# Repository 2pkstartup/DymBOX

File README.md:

# DymBOX

Regulátor teploty pro udírnu postavený na mikrokontroléru **ATmega8**.

Měří teplotu pomocí DS18B20, zobrazuje ji na 3-místném 7-segmentovém displeji a řídí ventilátor (PWM) a topnou spirálu (ON/OFF s hysterezí). Žádaná teplota a otáčky ventilátoru se nastavují rotačním enkodérem.

## Vlastnosti

- **Měření teploty** – DS18B20 (1-Wire), rozlišení 0.1 °C
- **3-místný 7-segment display** – multiplexovaný v Timer0 ISR (~163 Hz/číslice)
- **Rotační enkodér KY-040** – nastavení žádané teploty a otáček ventilátoru
- **PWM ventilátor** – 11 kroků (0–100 % po 10 %), Timer1 Fast PWM 8-bit na ~977 Hz
- **Topná spirála** – ON/OFF regulace s hysterezí 5 °C
- **Nastavitelný setpoint** – výchozí 32.0 °C, editace po 0.1 °C

## Struktura repozitáře

```
DymBOX/
├── fw/                 # Firmware (C, ATmega8)
│   ├── main.c
│   ├── CMakeLists.txt
│   ├── Makefile
│   ├── cmake/          # AVR-GCC toolchain soubor
│   └── README.md
├── hw/                 # Hardware (KiCad 8)
│   ├── DymBOX_AVR.kicad_sch    # Schéma
│   ├── DymBOX_AVR.kicad_pcb    # PCB layout
│   ├── gerber/                  # Gerber soubory pro výrobu
│   ├── dymbox_gerber.zip        # Zabalené gerbery
│   ├── 2pkstartup.pretty/      # Vlastní footprinty
│   └── DymBOX_AVR-backups/
└── README.md
```

## Hardware

Schéma a PCB jsou navrženy v **KiCadu**. Gerber soubory připravené k výrobě najdete v `hw/gerber/` nebo jako `hw/dymbox_gerber.zip`.

### Hlavní komponenty

| Součástka | Popis |
|-----------|-------|
| ATmega8 | Hlavní MCU (16 MHz) |
| DS18B20 | Digitální teploměr (1-Wire) |
| 3× 7-segment (common anode) | Displej – multiplexovaný |
| KY-040 | Rotační enkodér s tlačítkem |
| Ventilátor | PWM řízený (~977 Hz) |
| Topná spirála | ON/OFF přes PB2 |

### Zapojení pinů

```
PORTB: PB0 = seg A       PB1 = PWM fan    PB2 = heater
PORTC: PC0 = seg E       PC1 = seg D      PC2 = seg DP
       PC3 = seg C       PC4 = seg G      PC5 = DS18B20
PORTD: PD0 = ENC SW      PD1 = DIG3       PD2 = DIG2
       PD3 = ENC CLK     PD4 = ENC DT     PD5 = DIG1
       PD6 = seg B       PD7 = seg F
```

## Firmware

Firmware je napsaný v **C** pro AVR a překládá se pomocí `avr-gcc` + CMake.

### Požadavky

```bash
sudo apt install gcc-avr avr-libc binutils-avr avrdude cmake
```

### Kompilace a nahrání

```bash
cd fw
cmake -B build -DCMAKE_TOOLCHAIN_FILE=cmake/avr-gcc.cmake
cmake --build build              # Kompilace
cmake --build build --target flash   # Nahrání do MCU (USBasp)
cmake --build build --target fuses   # Nastavení fuses
```

### Velikost firmware

```
Program:  ~2186 bytes (26.7 % Flash)
Data:       ~61 bytes  (6.0 % SRAM)
```

## Ovládání

Zařízení má 3 režimy zobrazení:

| Režim | Displej | Ovládání |
|-------|---------|----------|
| **Teplota** (výchozí) | `XX.X` – aktuální teplota | Otočení → ventilátor · Stisk → editace setpointu |
| **Ventilátor** | `FXX` – rychlost v % | Otočení → změna po 10 % · Po 2 s → zpět na teplotu |
| **Editace setpointu** | `XX.X` + DP1 svítí | Otočení → změna po 0.1 °C · Stisk → uložit a zpět |

Topná spirála se indikuje rozsvícením DP3 (poslední tečka).

## Regulace teploty

ON/OFF regulace s hysterezí:

| Podmínka | Akce |
|----------|------|
| teplota ≤ setpoint − 5 °C | Spirála **ON** |
| teplota ≥ setpoint | Spirála **OFF** |
| v pásmu hystereze | Beze změny |

## Licence

Tento projekt je volně k použití.

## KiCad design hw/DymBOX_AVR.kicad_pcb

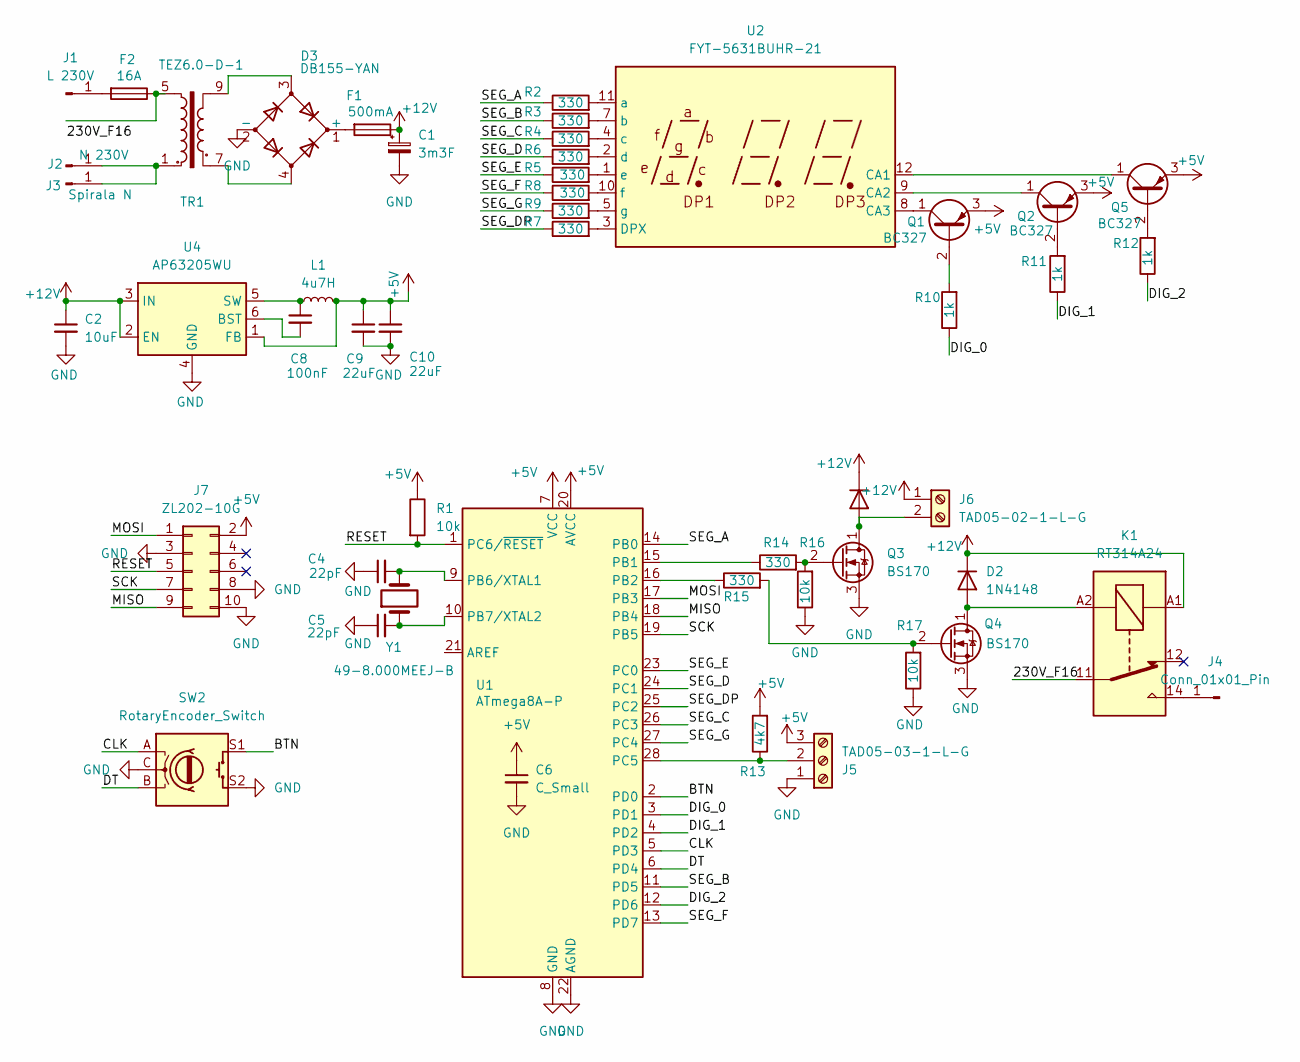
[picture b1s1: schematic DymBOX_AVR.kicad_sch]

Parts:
C1: 3m3F; CP_Radial_D16.0mm_P7.50mm
C2: 10uF; C_1206_3216Metric_Pad1.33x1.80mm_HandSolder
C4, C5: 22pF; C_0805_2012Metric_Pad1.18x1.45mm_HandSolder
C6: C_Small; C_0805_2012Metric_Pad1.18x1.45mm_HandSolder
C8: 100nF; C_0805_2012Metric_Pad1.18x1.45mm_HandSolder
C9, C10: 22uF; C_0805_2012Metric_Pad1.18x1.45mm_HandSolder
D1, D2: 1N4148; D_DO-35_SOD27_P7.62mm_Horizontal
D3: DB155-YAN; Diode_Bridge_DIP-4_W5.08mm_P2.54mm
F1: 500mA; Fuseholder_Clip-5x20mm_Littelfuse_111_Inline_P20.00x5.00mm_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
F2: 16A; Fuseholder_Clip-5x20mm_Littelfuse_111_Inline_P20.00x5.00mm_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
J1: L 230V; faston_6.3
J2: N 230V; faston_6.3
J3: Spirala N; faston_6.3
J4: Conn_01x01_Pin; faston_6.3
J5: TAD05-03-1-L-G; TerminalBlock_Phoenix_PT-1,5-3-3.5-H_1x03_P3.50mm_Horizontal
J6: TAD05-02-1-L-G; TerminalBlock_Phoenix_PT-1,5-2-3.5-H_1x02_P3.50mm_Horizontal
J7: ZL202-10G; PinHeader_2x05_P2.54mm_Vertical
K1: RT314A24; Relay_SPDT_Schrack-RT1-16A-FormC_RM5mm
L1: 4u7H; L_1210_3225Metric_Pad1.42x2.65mm_HandSolder
Q1, Q2, Q5: BC327; TO-92_HandSolder
Q3, Q4: BS170; TO-92_HandSolder
R1, R16, R17: 10k; R_Axial_DIN0204_L3.6mm_D1.6mm_P5.08mm_Horizontal
R2, R3, R4, R5, R6, R7, R8, R9, R14, R15: 330; R_Axial_DIN0204_L3.6mm_D1.6mm_P5.08mm_Horizontal
R10, R11, R12: 1k; R_Axial_DIN0204_L3.6mm_D1.6mm_P5.08mm_Horizontal
R13: 4k7; R_Axial_DIN0204_L3.6mm_D1.6mm_P5.08mm_Horizontal
SW2: RotaryEncoder_Switch; RotaryEncoder_Alps_EC12E-Switch_Vertical_H20mm_CircularMoun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
TR1: TEZ6.0-D-1; Transformer_Breve_TEZ-38x45
U1: ATmega8A-P; DIP-28_W7.62mm
U2: FYT-5631BUHR-21
U4: AP63205WU; TSOT-23-6
Y1: 49-8.000MEEJ-B; Crystal_HC49-U_Vertical

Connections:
+5V: C6.1, C9.1, C10.1, J5.3, J7.2, L1.2, Q1.3 (E), Q2.3 (E), Q5.3 (E), R1.1, R13.2, U1.7 (VCC), U1.20 (AVCC), U4.1 (FB)
+12V: C1.1, C2.1, D1.1 (K), D2.1 (K), F1.1, J6.1, K1.A1, U4.2 (EN), U4.3 (IN)
/BTN: SW2.S1, U1.2 (PD0)
/CLK: SW2.A, U1.5 (PD3)
/DIG_0: R10.1, U1.3 (PD1)
/DIG_1: R11.1, U1.4 (PD2)
/DIG_2: R12.1, U1.12 (PD6)
/DT: SW2.B, U1.6 (PD4)
/MISO: J7.9, U1.18 (PB4)
/MOSI: J7.1, U1.17 (PB3)
/RESET: J7.5, R1.2, U1.1 (PC6/~RESET)
/SCK: J7.7, U1.19 (PB5)
/SEG_A: R2.1, U1.14 (PB0)
/SEG_B: R3.1, U1.11 (PD5)
/SEG_C: R4.1, U1.26 (PC3)
/SEG_D: R6.1, U1.24 (PC1)
/SEG_DP: R7.1, U1.25 (PC2)
/SEG_E: R5.1, U1.23 (PC0)
/SEG_F: R8.1, U1.13 (PD7)
/SEG_G: R9.1, U1.27 (PC4)
GND: C1.2, C2.2, C4.1, C5.1, C6.2, C9.2, C10.2, D3.2 (-), J5.1, J7.3, J7.8, J7.10, Q3.3 (S), Q4.3 (S), R16.1, R17.1, SW2.C, SW2.S2, U1.8 (GND), U1.22 (AGND), U4.4 (GND)
unnamed: D1.2 (A), J6.2, Q3.1 (D)
unnamed: D2.2 (A), K1.A2, Q4.1 (D)
unnamed: D3.1 (+), F1.2
unnamed: D3.3, TR1.9
unnamed: D3.4, TR1.7
unnamed: F2.2, J1.1 (Pin_1_1)
unnamed: J2.1 (Pin_1_1), J3.1 (Pin_1_1), TR1.1
unnamed: J4.1 (Pin_1_1), K1.14
unnamed: J5.2, R13.1, U1.28 (PC5)
unnamed: Q1.2 (B), R10.2
unnamed: Q1.1 (C), U2.8 (CA3)
unnamed: Q2.2 (B), R11.2
unnamed: Q2.1 (C), U2.9 (CA2)
unnamed: Q3.2 (G), R14.2, R16.2
unnamed: Q4.2 (G), R15.2, R17.2
unnamed: Q5.2 (B), R12.2
unnamed: Q5.1 (C), U2.12 (CA1)
unnamed: R14.1, U1.15 (PB1)
unnamed: R15.1, U1.16 (PB2)
unnamed: C4.2, U1.9 (PB6/XTAL1), Y1.2
unnamed: C5.2, U1.10 (PB7/XTAL2), Y1.1
unnamed: R7.2, U2.3 (DPX)
unnamed: R2.2, U2.11 (a)
unnamed: R3.2, U2.7 (b)
unnamed: R4.2, U2.4 (c)
unnamed: R6.2, U2.2 (d)
unnamed: R5.2, U2.1 (e)
unnamed: R8.2, U2.10 (f)
unnamed: R9.2, U2.5 (g)
unnamed: C8.2, U4.6 (BST)
unnamed: C8.1, L1.1, U4.5 (SW)

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
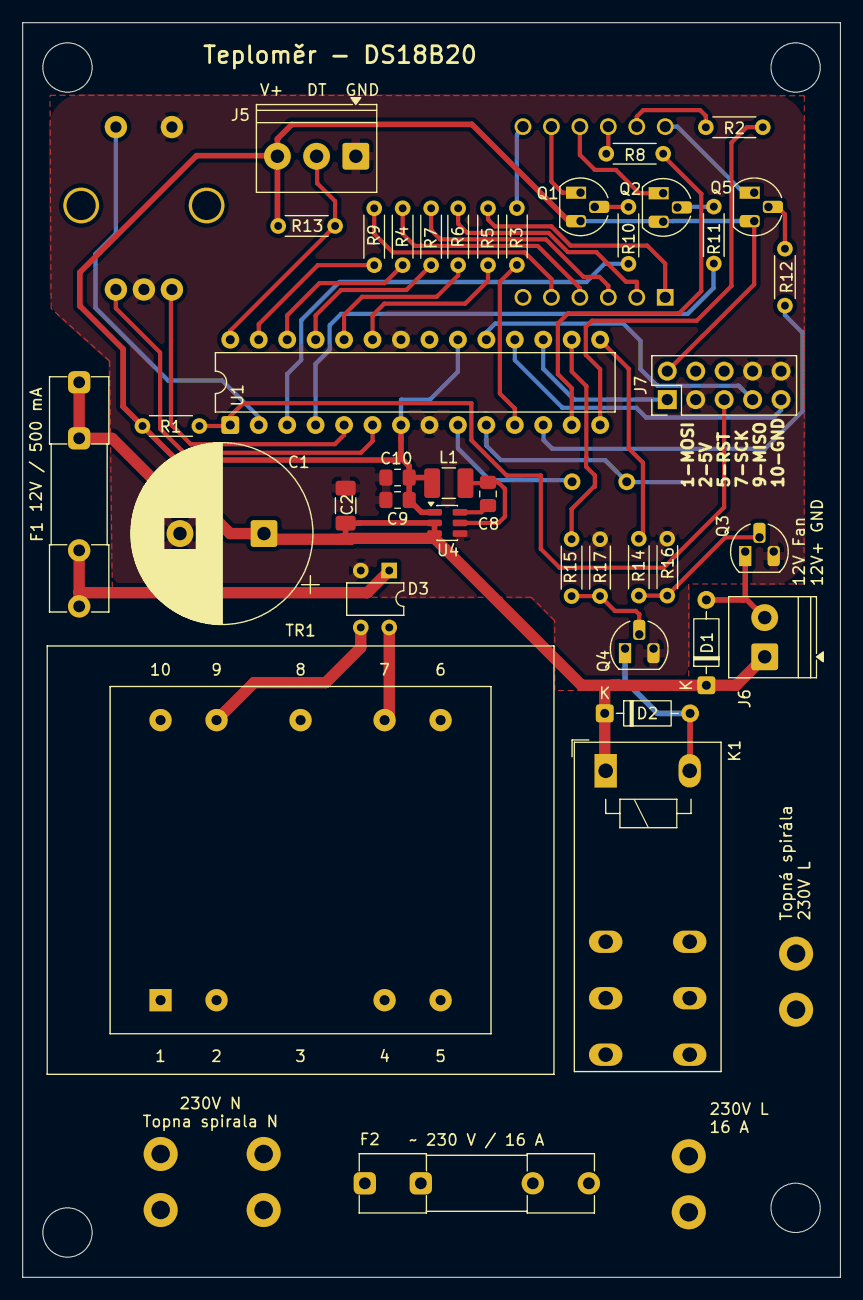
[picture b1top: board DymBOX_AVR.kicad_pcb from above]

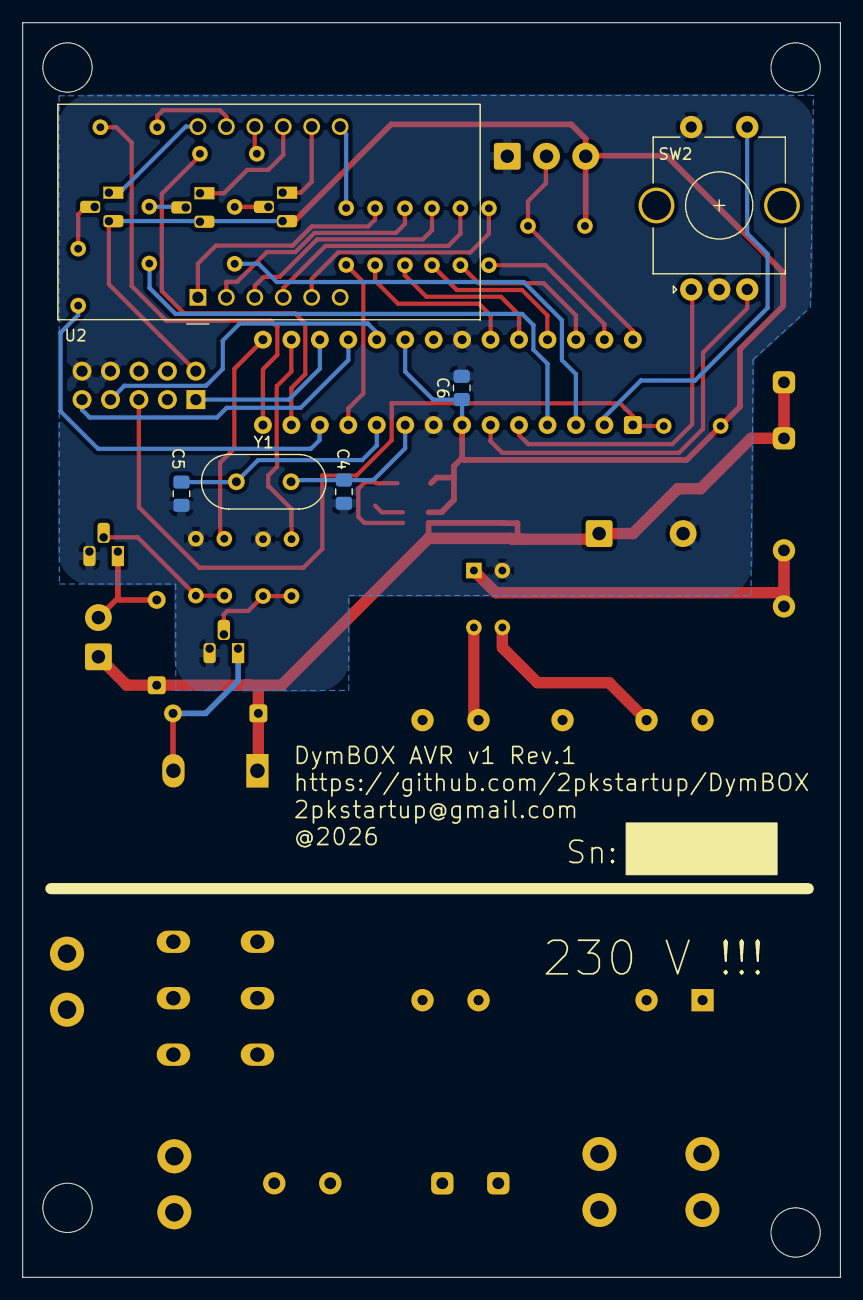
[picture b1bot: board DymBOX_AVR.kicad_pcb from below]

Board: 2 copper layers, 73.0 x 112.0 mm, 50 parts (6 on the bottom side), 53 nets.

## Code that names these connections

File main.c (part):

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 *
 * Zapojení pinů ATmega8 (DIP-28):
 *
 *   PORTB:  PB0 = seg A (display)
 *           PB1 = OC1A - PWM ventilátor (active HIGH)
 *           PB2 = topná spirála (active HIGH)
 *           PB3..PB5 = ISP (MOSI, MISO, SCK) / volné
 *
 *   PORTC:  PC0 = seg E        PC3 = seg C
 *           PC1 = seg D        PC4 = seg G
 *           PC2 = seg DP       PC5 = DS18B20 DQ (+ 4.7kΩ pull-up)
 *
 *   PORTD:  PD0 = ENC SW (tlačítko) PD3 = ENC CLK (A)
 *           PD1 = DIG3 (jednotky)   PD4 = ENC DT  (B)
 *           PD2 = DIG2 (desítky)    PD5 = DIG1 (stovky)
 *           PD6 = seg B             PD7 = seg F
 *
 * Schéma:
 *
 *                         ATmega8 (DIP-28)
 *                      ┌────────────────────┐
 *         seg A ← PB0 ─┤1  (PC5) RESET   28├─ PC5 → DS18B20 DQ
 *     PWM fan ← PB1 ─┤2  (PC4)  ADC5   27├─ PC4 → seg G
 *      heater ← PB2 ─┤3  (PC3)  ADC4   26├─ PC3 → seg C
 *    ISP MOSI   PB3 ─┤4  (PC2)  ADC3   25├─ PC2 → seg DP
 *    ISP MISO   PB4 ─┤5  (PC1)  ADC2   24├─ PC1 → seg D
 *     ISP SCK   PB5 ─┤6  (PC0)  ADC1   23├─ PC0 → seg E
 *                     ─┤7  AVCC         22├─ GND
 *                     ─┤8  AREF         21├─ AREF
 *               VCC  ─┤9  VCC          20├─ VCC
 *               GND  ─┤10 GND          19├─ PB5 (SCK)
 *              XTAL1 ─┤11              18├─ PB4 (MISO)
 *              XTAL2 ─┤12              17├─ PB3 (MOSI)
 *      ENC SW → PD0 ─┤13 (RXD)        16├─ PB2 → heater
 *        DIG3 ← PD1 ─┤14 (TXD)        15├─ PB1 → PWM fan
 *        DIG2 ← PD2 ─┤15 (INT0)       14├─ PD7 → seg F
 *     ENC CLK → PD3 ─┤16 (INT1)       13├─ PD6 → seg B
 *      ENC DT → PD4 ─┤17 (T0)
 *        DIG1 ← PD5 ─┤18 (T1)
 *                      └────────────────────┘
 *
 *   Display: common anode, segmenty active LOW
 *   Digit select: active LOW (PNP/P-FET)
 *   Výstupy PB1, PB2: active HIGH (pro D4184 MOSFET moduly)
 *   DS18B20: externě 4.7 kΩ pull-up na VCC
 *   KY-040: interní pull-up na PD3, PD4, PD5
 *   F_CPU = 16 MHz
 *
 * Konstanty:
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#include <util/delay.h>

/* Masky segmentových pinů na jednotlivých portech */
#define SEG_B_MASK  ((1 << PB0))                                          /* A */
#define SEG_C_MASK  ((1 << PC0)|(1 << PC1)|(1 << PC2)|(1 << PC3)|(1 << PC4)) /* G,C,D,DP,E */
#define SEG_D_MASK  ((1 << PD6)|(1 << PD7))                              /* B,F */

/* Maska digit-select pinů na PORTD */
#define DIG_MASK    ((1 << PD1)|(1 << PD2)|(1 << PD5))

/* Rotační enkodér KY-040 na PORTD */
#define ENC_CLK     PD3
#define ENC_DT      PD4
#define ENC_SW      PD0
#define ENC_MASK    ((1 << ENC_CLK)|(1 << ENC_DT)|(1 << ENC_SW))

/* DS18B20 1-Wire na PC5 */
#define OW_DDR      DDRC
#define OW_PORT     PORTC
#define OW_PIN      PINC
#define OW_BIT      PC5

/* PWM výstupy */
#define PWM1_PIN    PB1   /* OC1A - ventilátor */
#define PWM2_PIN    PB2   /* topná spirála (SW ON/OFF) */

/* Topná spirála: konstanty */
#define HEATER_PERIOD  4880   /* 10 s perioda (488 Hz × 10) */
#define HEATER_HYST    25     /* hystereze 5.0°C (v 1/10 °C) */

/* Pin pro každou pozici: DIG1(stovky)=PD5, DIG2(desítky)=PD2, DIG3(jednotky)=PD1 */
static const uint8_t dig_pin[] = {PD5, PD2, PD1};

/*
 * Lookup tabulky: bity = piny, které mají být LOW (aktivní) pro danou číslici.
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 *   Seg ON:  ABCDEF BC   ABDEG ABCDG BCFG  ACDFG ACDEFG ABC  ABCDEFG ABCDFG
 */

/*         A=PB0 */
static const uint8_t seg_b[] = {
    0x01, /* 0: A */
    0x00, /* 1:   */
    0x01, /* 2: A */
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    0x01, /* 9: A */
};

/*         E=PC0  D=PC1  DP=PC2  C=PC3  G=PC4 */
static const uint8_t seg_c[] = {
    0x0B, /* 0: C,D,E         = (1<<3)|(1<<1)|(1<<0) */
    0x08, /* 1: C             = (1<<3) */
    0x13, /* 2: D,E,G         = (1<<1)|(1<<0)|(1<<4) */
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    0x1A, /* 9: C,D,G         = (1<<3)|(1<<1)|(1<<4) */
};

/*         B=PD6  F=PD7 */
static const uint8_t seg_d[] = {
    0xC0, /* 0: B,F  = (1<<6)|(1<<7) */
    0x40, /* 1: B    = (1<<6) */
    0x40, /* 2: B    = (1<<6) */
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
static void display_init(void)
{
    /* PORTB: PB0 výstup (seg A), PB1/PB2 výstup (active HIGH, start LOW), ostatní pull-up */
    DDRB  = SEG_B_MASK | (1 << PWM1_PIN) | (1 << PWM2_PIN);
    PORTB = 0xFF & ~(1 << PWM1_PIN) & ~(1 << PWM2_PIN);  /* PB1,PB2 start LOW */

    /* PORTC: PC0-PC4 výstup (segmenty), PC5 vstup s pull-up (1-Wire idle) */
    DDRC  = SEG_C_MASK;
    PORTC = 0x3F;

    /* PORTD: PD1,PD2,PD5 výstup (digit), PD6-PD7 výstup (seg B,F), PD0,PD3,PD4 vstup s pull-up */
    DDRD  = DIG_MASK | SEG_D_MASK;  /* PD0,PD3,PD4 zůstávají vstup */
    PORTD = 0xFF;                   /* pull-up na všech (i enkodér) */

    /* Timer0: prescaler 64, overflow interrupt */
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    disp_d[pos] = seg_d[value];

    if (dp)
        disp_c[pos] |= (1 << PC2);  /* DP ON (active LOW = přidat do active masky) */
}

/* Zhasnout celý display */
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
    disp_b[0] = seg_b[d0]; disp_c[0] = seg_c[d0]; disp_d[0] = seg_d[d0];
    /* DIG2 s desetinnou tečkou */
    disp_b[1] = seg_b[d1]; disp_c[1] = seg_c[d1] | (1 << PC2); disp_d[1] = seg_d[d1];
    /* DIG3: DP3 svítí když topí spirála */
    disp_b[2] = seg_b[d2]; disp_c[2] = seg_c[d2]; disp_d[2] = seg_d[d2];
    if (heater_active)
        disp_c[2] |= (1 << PC2);
}

/* Zobrazit žádanou hodnotu: XX.X s DP1 (první tečka) jako indikace editačního režimu */
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    uint8_t d0 = sp_x10 % 10;

    /* DIG1 s DP (indikace edit módu) */
    disp_b[0] = seg_b[d0]; disp_c[0] = seg_c[d0] | (1 << PC2); disp_d[0] = seg_d[d0];
    /* DIG2 s desetinnou tečkou */
    disp_b[1] = seg_b[d1]; disp_c[1] = seg_c[d1] | (1 << PC2); disp_d[1] = seg_d[d1];
    disp_b[2] = seg_b[d2]; disp_c[2] = seg_c[d2]; disp_d[2] = seg_d[d2];
}

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    _delay_ms(50);  /* krátký debounce po uvolnění */
}

/* ====== PWM ventilátor (Timer1, OC1A = PB1) ====== */

/* Invertovaná tabulka: 0%=0(LOW), 10%=25, ... 100%=255(HIGH) */
static const uint8_t pwm_table[] = {
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
static void pwm_init(void)
{
    /* Timer1: Fast PWM 8-bit, non-inverting na OC1A (PB1) */
    /* HIGH když counter < OCR1A, LOW když counter >= OCR1A */
    /* 16 MHz / 64 / 256 = ~977 Hz (D4184 nezvládá vysoké frekvence) */
    TCCR1A = (1 << COM1A1) | (1 << WGM10);
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}

/* Zobrazit fan speed: "FXX" (0-90%) nebo "100" */
#define CHAR_F_B  0x01        /* A=PB0 */
#define CHAR_F_C  0x11        /* E=PC0, G=PC4 */
#define CHAR_F_D  0x80        /* F=PD7 */

static void display_fan(uint8_t fan_pct)
{
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    }
}

/* ====== Topná spirála (ON/OFF s hysterezí, PB2) ====== */

static void heater_set(uint8_t on)
{
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
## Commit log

2026-03-12 Initial commit: ATmega8 3-digit 7-segment display driver
2026-03-12 Add rotary encoder KY-040 support (PD3/PD4/PD5)
2026-03-12 Add temperature setpoint editing via encoder with DP1 indicator
2026-03-12 Add detailed README.md
2026-03-12 Store setpoint in EEPROM with magic byte validation
2026-03-13 Add comprehensive header comment with pinout diagram and description
2026-04-07 init
2026-04-07 readresace
2026-04-08 pcb_f
2026-04-09 pcb_transfo
2026-04-09 oprava readme
2026-04-10 prace
2026-04-10 uprava a více
2026-04-10 remove
2026-04-10 úpravy
2026-04-11 AP63005
2026-04-13 pojistka16A a další
2026-04-13 final v01
2026-04-13 final v02
2026-04-14 3d modely
2026-04-28 final assembly finish
